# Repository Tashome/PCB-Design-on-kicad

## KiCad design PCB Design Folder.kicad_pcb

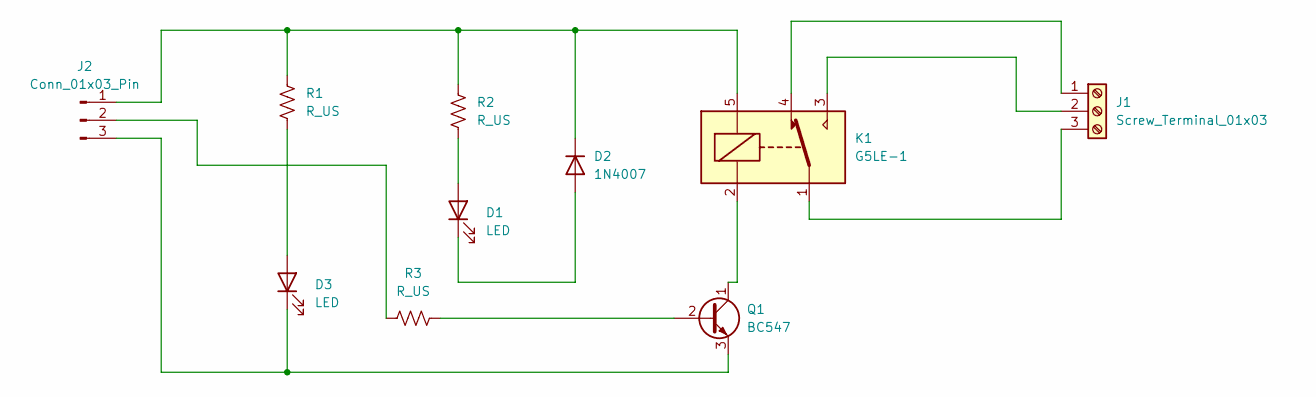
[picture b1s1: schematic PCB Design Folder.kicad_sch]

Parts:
D1, D3: LED; LED_D3.0mm
D2: 1N4007; D_DO-41_SOD81_P10.16mm_Horizontal
J1: Screw_Terminal_01x03; Altech_AK300_1x03_P5.00mm_45-Degree
J2: Conn_01x03_Pin; PinHeader_1x03_P1.27mm_Vertical_SMD_Pin1Left
K1: G5LE-1; Relay_SPDT_Omron-G5LE-1
Q1: BC547; TO-92_Inline
R1, R2, R3: R_US; R_Axial_DIN0204_L3.6mm_D1.6mm_P5.08mm_Horizontal

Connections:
unnamed: D1.2 (A), R2.2
unnamed: D1.1 (K), D2.2 (A)
unnamed: D2.1 (K), J2.1, K1.5, R1.1, R2.1
unnamed: D3.2 (A), R1.2
unnamed: D3.1 (K), J2.3, Q1.3 (E)
unnamed: J1.1, K1.4
unnamed: J1.2, K1.3
unnamed: J1.3, K1.1
unnamed: J2.2, R3.1
unnamed: Q1.2 (B), R3.2
unnamed: K1.2, Q1.1 (C)

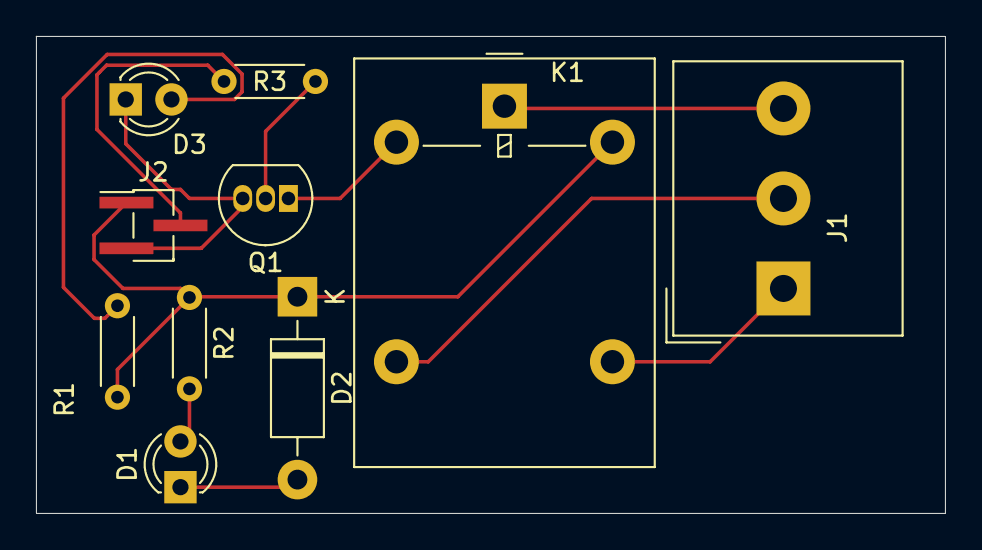
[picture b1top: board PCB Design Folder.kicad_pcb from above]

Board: 2 copper layers, 50.5 x 26.5 mm, 10 parts (0 on the bottom side), 11 nets.

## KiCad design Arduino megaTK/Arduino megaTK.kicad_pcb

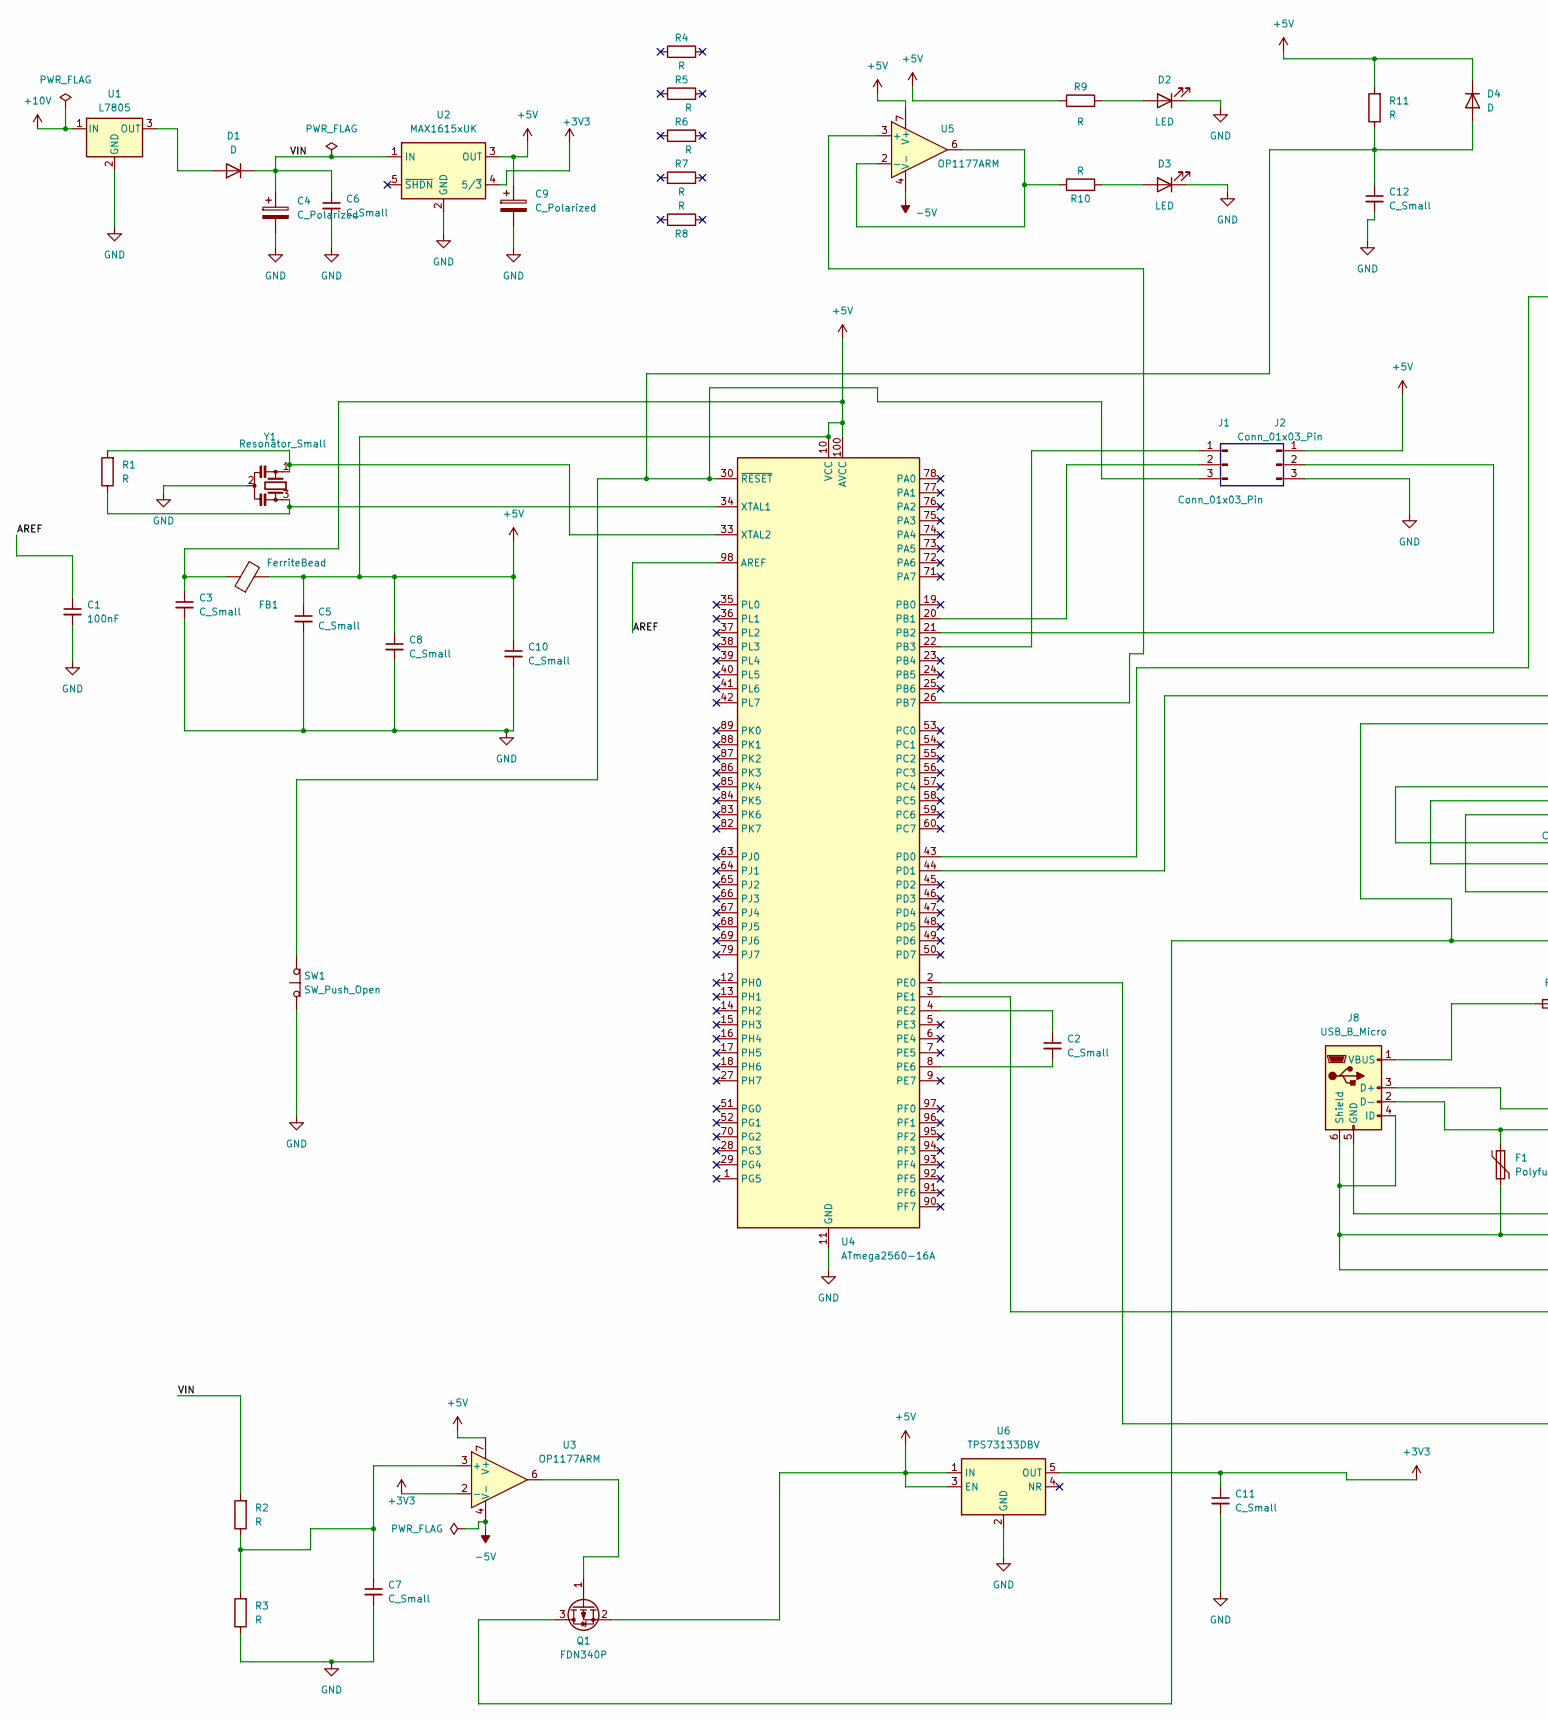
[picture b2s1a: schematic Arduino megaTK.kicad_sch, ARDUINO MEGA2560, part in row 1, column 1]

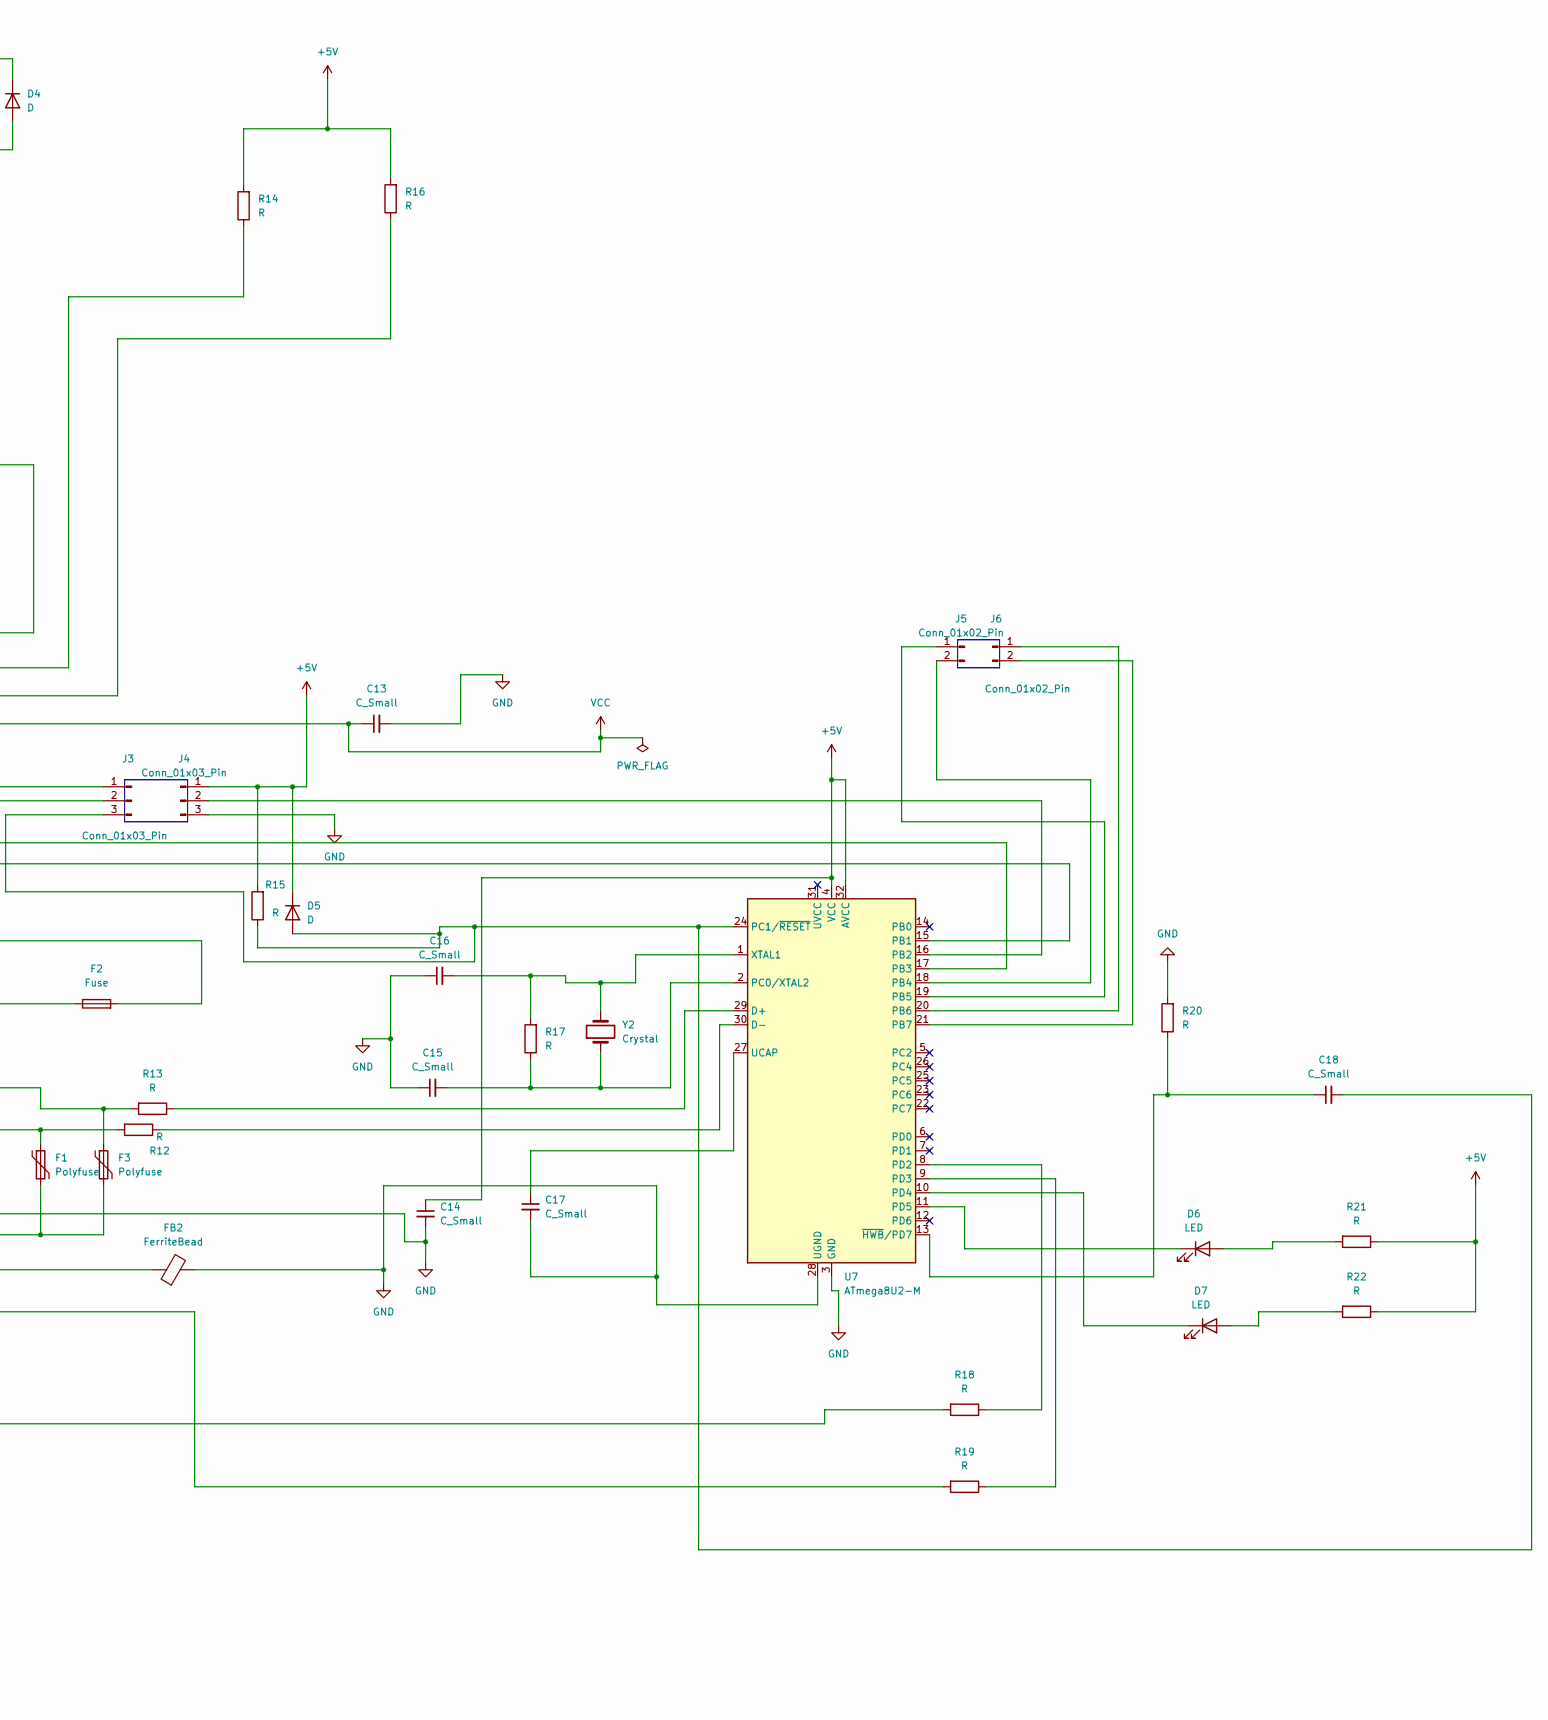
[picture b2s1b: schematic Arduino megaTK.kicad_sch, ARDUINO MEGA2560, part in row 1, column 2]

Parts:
C1: 100nF; C_0603_1608Metric
C2, C3, C5, C6, C7, C8, C10, C11, C12, C13, C14, C15, C16, C17, C18: C_Small; C_0603_1608Metric
C4, C9: C_Polarized; CP_Radial_D4.0mm_P1.50mm
D1, D4, D5: D; D_0805_2012Metric
D2, D3, D6, D7: LED; LED_0805_2012Metric_Pad1.15x1.40mm_HandSolder
F1, F3: Polyfuse; Fuse_1206_3216Metric_Pad1.42x1.75mm_HandSolder
F2: Fuse; Fuse_0603_1608Metric
FB1, FB2: FerriteBead; L_0603_1608Metric
J1, J2, J3, J4: Conn_01x03_Pin; PinHeader_1x03_P2.54mm_Vertical
J5, J6: Conn_01x02_Pin; PinHeader_1x02_P2.54mm_Vertical
J8: USB_B_Micro; USB_Mini-B_Lumberg_2486_01_Horizontal
Q1: FDN340P; SOT-23
R1, R2, R3, R4, R5, R6, R7, R8, R9, R10, R11, R12, R13, R14, R15, R16, R17, R18, R19, R20, R21, R22: R; R_0603_1608Metric
SW1: SW_Push_Open; SW_SPST_PTS645
U1: L7805; BarrelJack_Horizontal
U2: MAX1615xUK; SOT-23-5
U3, U5: OP1177ARM; MSOP-8_3x3mm_P0.65mm
U4: ATmega2560-16A; TQFP-100_14x14mm_P0.5mm
U6: TPS73133DBV; SOT-23-5
U7: ATmega8U2-M; QFN-32-1EP_5x5mm_P0.5mm_EP3.3x3.3mm_ThermalVias
Y1: Resonator_Small; Resonator_SMD-3Pin_7.2x3.0mm
Y2: Crystal; Resonator_SMD_Murata_CDSCB-2Pin_4.5x2.0mm

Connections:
+3V3: C11.1, U2.4 (5/~3), U3.2 (-), U6.5 (OUT)
+5V: C3.1, C5.1, C8.1, C9.1, C10.1, C14.1, D4.1 (K), D5.1 (K), FB1.1, FB1.2, J2.1, J4.1, Q1.2 (S), R9.1, R11.2, R14.2, R15.2, R16.2, R21.1, R22.1, U2.3 (OUT), U3.7 (V+), U4.10 (VCC), U4.31 (VCC), U4.61 (VCC), U4.80 (VCC), U4.100 (AVCC), U5.7 (V+), U6.1 (IN), U6.3 (EN), U7.4 (VCC), U7.32 (AVCC)
+10V: U1.1 (IN)
-5V: U3.4 (V-), U5.4 (V-)
/AREF: C1.1, U4.98 (AREF)
/VIN: C4.1, C6.1, D1.1 (K), R2.2, U2.1 (IN)
GND: C1.2, C3.2, C4.2, C5.2, C6.2, C7.2, C8.2, C9.2, C10.2, C11.2, C12.2, C13.2, C14.2, C15.1, C16.1, C17.2, D2.1 (K), D3.1 (K), FB2.2, J2.3, J4.3, J8.5 (GND), R3.1, R20.2, SW1.1 (A), U1.2 (GND), U2.2 (GND), U4.11 (GND), U4.32 (GND), U4.62 (GND), U4.81 (GND), U4.99 (GND), U6.2 (GND), U7.3 (GND), U7.28 (UGND), U7.33 (GND), Y1.2
unnamed: D1.2 (A), U1.3 (OUT)
unnamed: D2.2 (A), R9.2
unnamed: D3.2 (A), R10.2
unnamed: C12.1, D4.2 (A), J1.3, R11.1, SW1.2 (B), U4.30 (~RESET)
unnamed: C18.2, D5.2 (A), J3.3, R15.1, U7.24 (PC1/~RESET)
unnamed: D6.2 (A), R21.2
unnamed: D6.1 (K), U7.11 (PD5)
unnamed: D7.2 (A), R22.2
unnamed: D7.1 (K), U7.10 (PD4)
unnamed: J1.1, U4.22 (PB3)
unnamed: J1.2, U4.20 (PB1)
unnamed: J2.2, U4.21 (PB2)
unnamed: J3.1, U7.17 (PB3)
unnamed: J3.2, U7.15 (PB1)
unnamed: J4.2, U7.16 (PB2)
unnamed: J5.1, U7.19 (PB5)
unnamed: J5.2, U7.18 (PB4)
unnamed: J6.1, U7.20 (PB6)
unnamed: J6.2, U7.21 (PB7)
unnamed: F3.1, J8.3 (D+), R13.2
unnamed: F1.1, J8.2 (D-), R12.2
unnamed: F1.2, F3.2, FB2.1, J8.4 (ID), J8.6 (Shield)
unnamed: F2.1, J8.1 (VBUS)
unnamed: Q1.1 (G), U3.6
unnamed: C7.1, R2.1, R3.2, U3.3 (+)
unnamed: U4.26 (PB7), U5.3 (+)
unnamed: R14.1, U4.43 (PD0)
unnamed: R16.1, U4.44 (PD1)
unnamed: R18.2, U4.2 (PE0)
unnamed: R19.2, U4.3 (PE1)
unnamed: C2.1, U4.4 (PE2)
unnamed: C2.2, U4.8 (PE6)
unnamed: R1.1, U4.34 (XTAL1), Y1.3
unnamed: R1.2, U4.33 (XTAL2), Y1.1
unnamed: R10.1, U5.2 (-), U5.6
unnamed: R13.1, U7.29 (D+)
unnamed: R12.1, U7.30 (D-)
unnamed: C15.2, R17.1, U7.2 (PC0/XTAL2), Y2.1
unnamed: R18.1, U7.8 (PD2)
unnamed: R19.1, U7.9 (PD3)
unnamed: C17.1, U7.27 (UCAP)
unnamed: C16.2, R17.2, U7.1 (XTAL1), Y2.2
unnamed: C18.1, R20.1, U7.13 (~HWB/PD7)
VCC: C13.1, F2.2, Q1.3 (D)

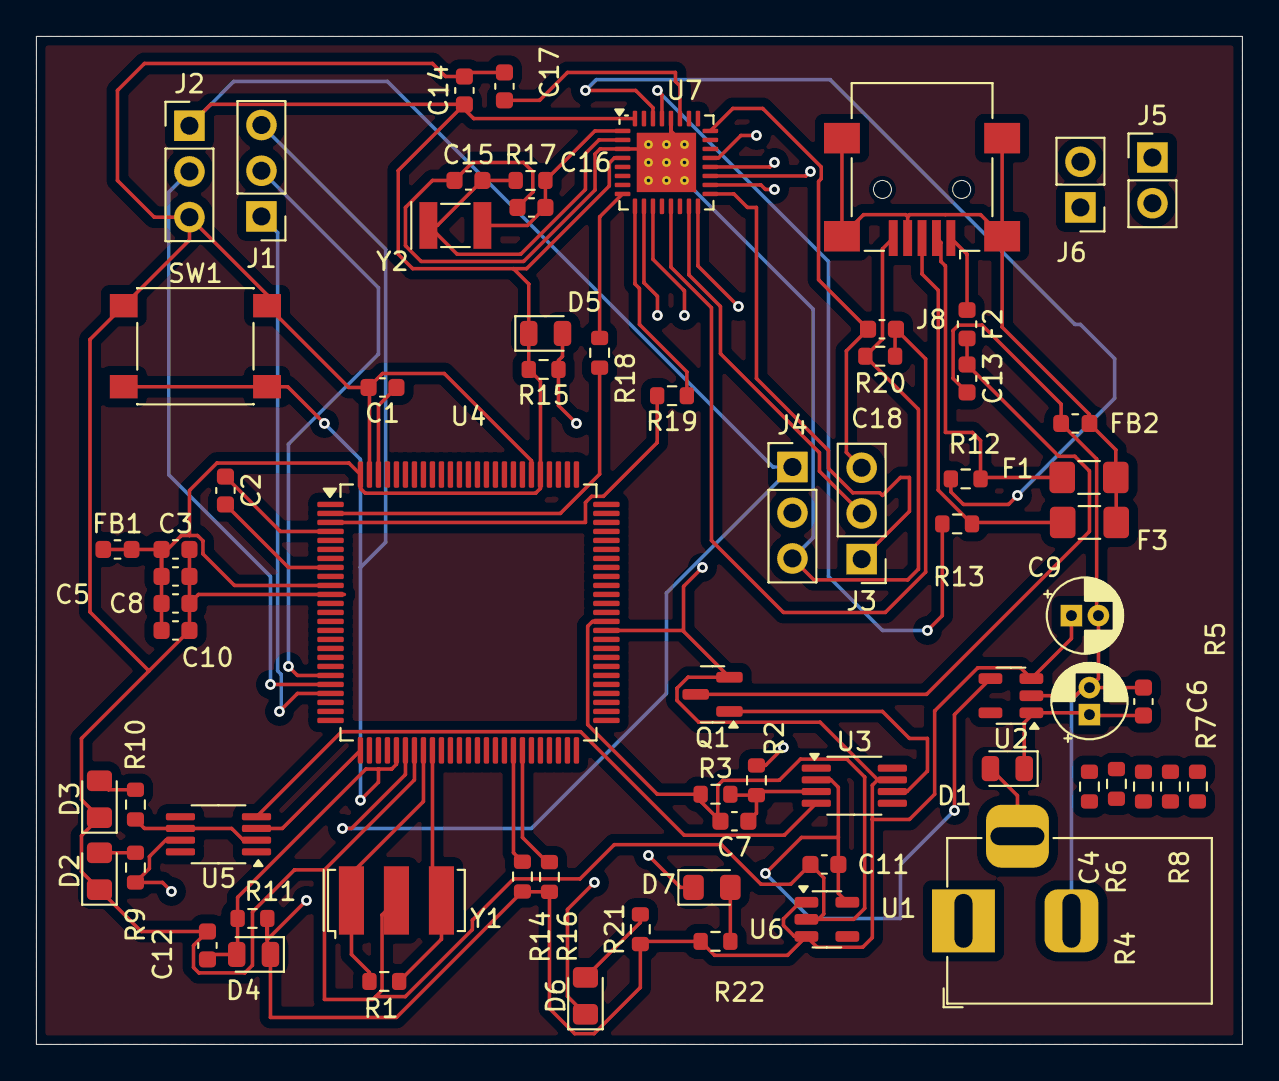
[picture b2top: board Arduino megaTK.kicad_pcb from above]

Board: 4 copper layers, 67.0 x 56.0 mm, 70 parts (0 on the bottom side), 50 nets.

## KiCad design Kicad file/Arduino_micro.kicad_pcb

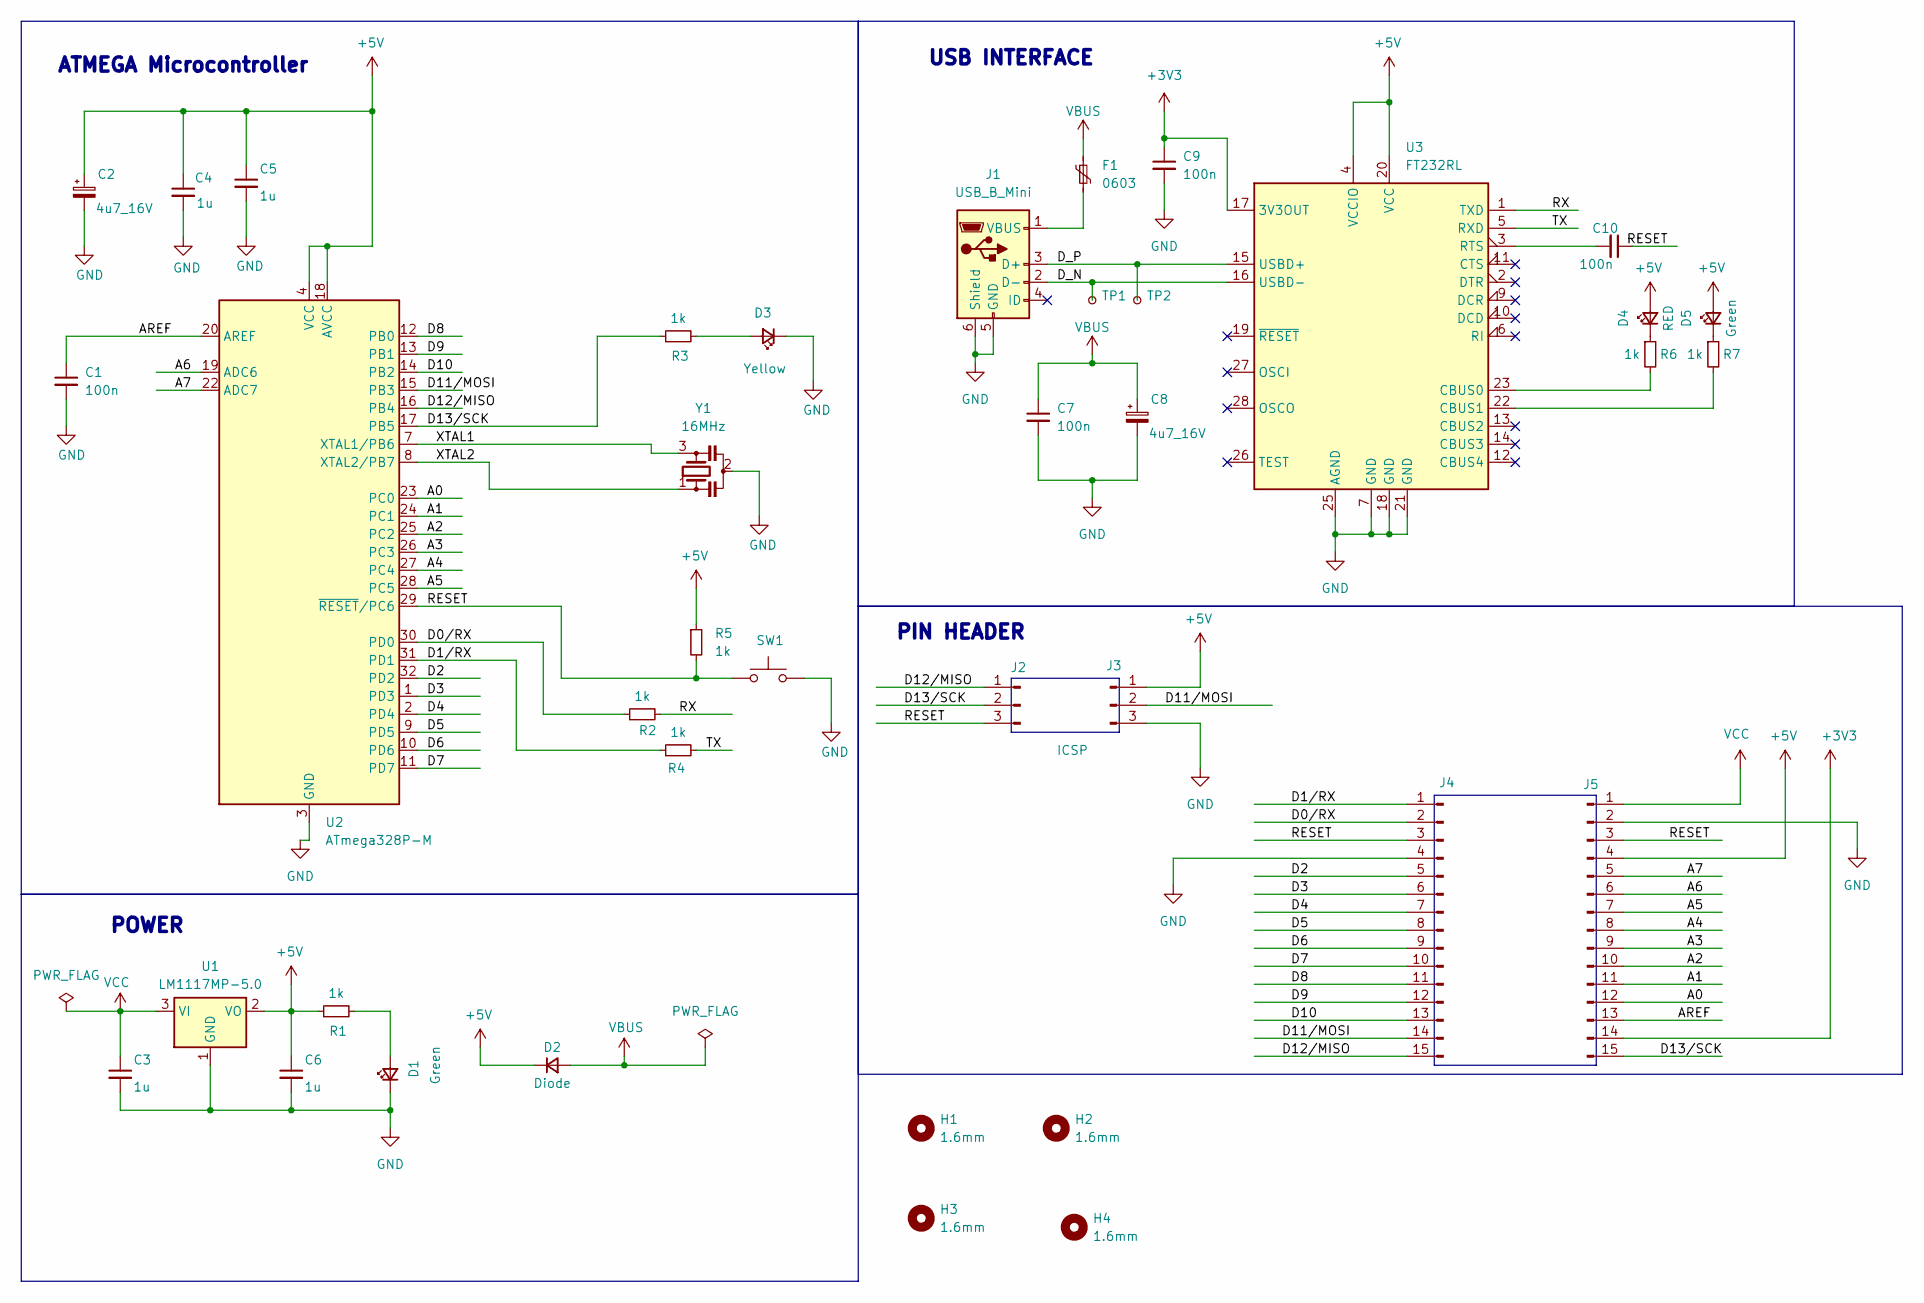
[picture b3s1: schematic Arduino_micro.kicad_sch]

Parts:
C1, C7, C9, C10: 100n; C_0603_1608Metric
C2, C8: 4u7_16V; CP_EIA-3216-10_Kemet-I
C3, C4, C5, C6: 1u; C_0603_1608Metric
D1, D5: Green; LED_0805_2012Metric
D2: Diode; D_MicroSMP_AK
D3: Yellow; LED_0805_2012Metric
D4: RED; LED_0805_2012Metric
F1: 0603; D_0603_1608Metric
H1, H2, H3, H4: 1.6mm; MountingHole_2mm
J1: USB_B_Mini; USB_Mini-B_Lumberg_2486_01_Horizontal
J2: PinHeader_1x03_P2.54mm_Vertical
J3: ICSP; PinHeader_1x03_P2.54mm_Vertical
J4, J5: PinHeader_1x15_P2.54mm_Vertical
R1, R2, R3, R4, R5, R6, R7: 1k; R_0603_1608Metric
SW1: SW_Push; SW_DIP_SPSTx01_Slide_9.78x4.72mm_W7.62mm_P2.54mm
TP1, TP2: TestPoint_Pad_D1.0mm
U1: LM1117MP-5.0; SOT-223-3_TabPin2
U2: ATmega328P-M; QFN-32-1EP_5x5mm_P0.5mm_EP3.1x3.1mm
U3: FT232RL; SSOP-28_5.3x10.2mm_P0.65mm
Y1: 16MHz; Resonator_SMD_Murata_CSTxExxV-3Pin_3.0x1.1mm

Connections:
+3V3: C9.1, J5.14, U3.17 (3V3OUT)
/A0: J5.12, U2.23 (PC0)
/A1: J5.11, U2.24 (PC1)
/A2: J5.10, U2.25 (PC2)
/A3: J5.9, U2.26 (PC3)
/A4: J5.8, U2.27 (PC4)
/A5: J5.7, U2.28 (PC5)
/A6: J5.6, U2.19 (ADC6)
/A7: J5.5, U2.22 (ADC7)
/AREF: C1.1, J5.13, U2.20 (AREF)
/D0/RX: J4.2, R2.1, U2.30 (PD0)
/D1/RX: J4.1, R4.1, U2.31 (PD1)
/D2: J4.5, U2.32 (PD2)
/D3: J4.6, U2.1 (PD3)
/D4: J4.7, U2.2 (PD4)
/D5: J4.8, U2.9 (PD5)
/D6: J4.9, U2.10 (PD6)
/D7: J4.10, U2.11 (PD7)
/D8: J4.11, U2.12 (PB0)
/D9: J4.12, U2.13 (PB1)
/D10: J4.13, U2.14 (PB2)
/D11/MOSI: J3.2, J4.14, U2.15 (PB3)
/D12/MISO: J2.1, J4.15, U2.16 (PB4)
/D13/SCK: J2.2, J5.15, R3.1, U2.17 (PB5)
/D_N: J1.2 (D-), TP1.1, U3.16 (USBD-)
/D_P: J1.3 (D+), TP2.1, U3.15 (USBD+)
/RESET: C10.1, J2.3, J4.3, J5.3, R5.2, SW1.1, U2.29 (~RESET/PC6)
/RX: R2.2, U3.1 (TXD)
/TX: R4.2, U3.5 (RXD)
/XTAL1: U2.7 (XTAL1/PB6), Y1.3
/XTAL2: U2.8 (XTAL2/PB7), Y1.1
GND: C1.2, C2.2, C3.2, C4.2, C5.2, C6.2, C7.2, C8.2, C9.2, D1.1 (K), D3.1 (K), J1.5 (GND), J1.6 (Shield), J3.3, J4.4, J5.2, SW1.2, U1.1 (GND), U2.3 (GND), U2.5 (GND), U2.21 (GND), U2.33 (GND), U3.7 (GND), U3.18 (GND), U3.21 (GND), U3.25 (AGND), Y1.2; also elsewhere on the board
unnamed: D1.2 (A), R1.2
unnamed: D3.2 (A), R3.2
unnamed: D4.1 (K), R6.1
unnamed: D5.1 (K), R7.1
unnamed: F1.2, J1.1 (VBUS)
unnamed: R6.2, U3.23 (CBUS0)
unnamed: R7.2, U3.22 (CBUS1)
unnamed: C10.2, U3.3 (RTS)
VCC: C3.1, J5.1, U1.3 (VI)

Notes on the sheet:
ATMEGA Microcontroller
PIN HEADER
USB INTERFACE
POWER

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
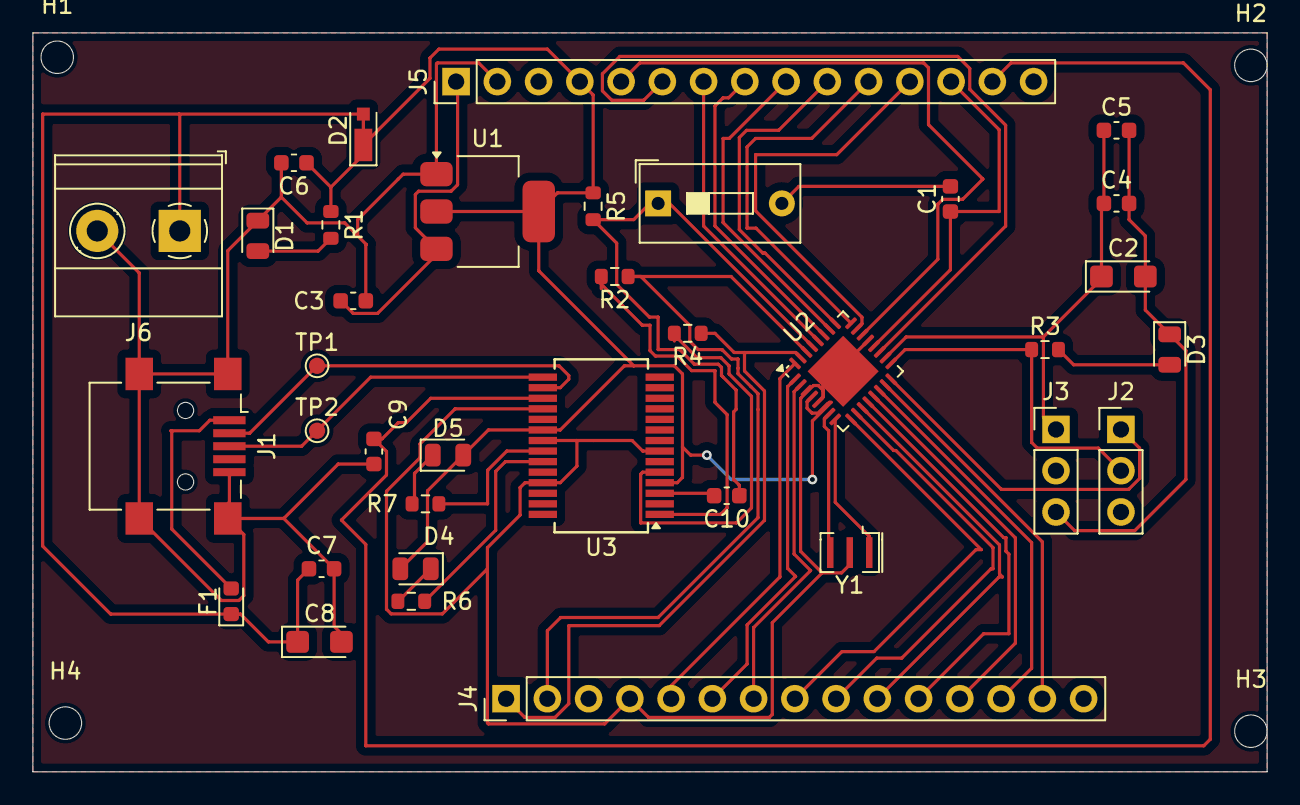
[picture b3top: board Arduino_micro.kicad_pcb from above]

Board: 4 copper layers, 76.0 x 45.5 mm, 40 parts (0 on the bottom side), 42 nets.

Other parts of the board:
J6: Screw_Terminal_01x02; TerminalBlock_Phoenix_MKDS-1,5-2-5.08_1x02_P5.08mm_Horizont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

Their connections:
GND: J6.2; also elsewhere on the board

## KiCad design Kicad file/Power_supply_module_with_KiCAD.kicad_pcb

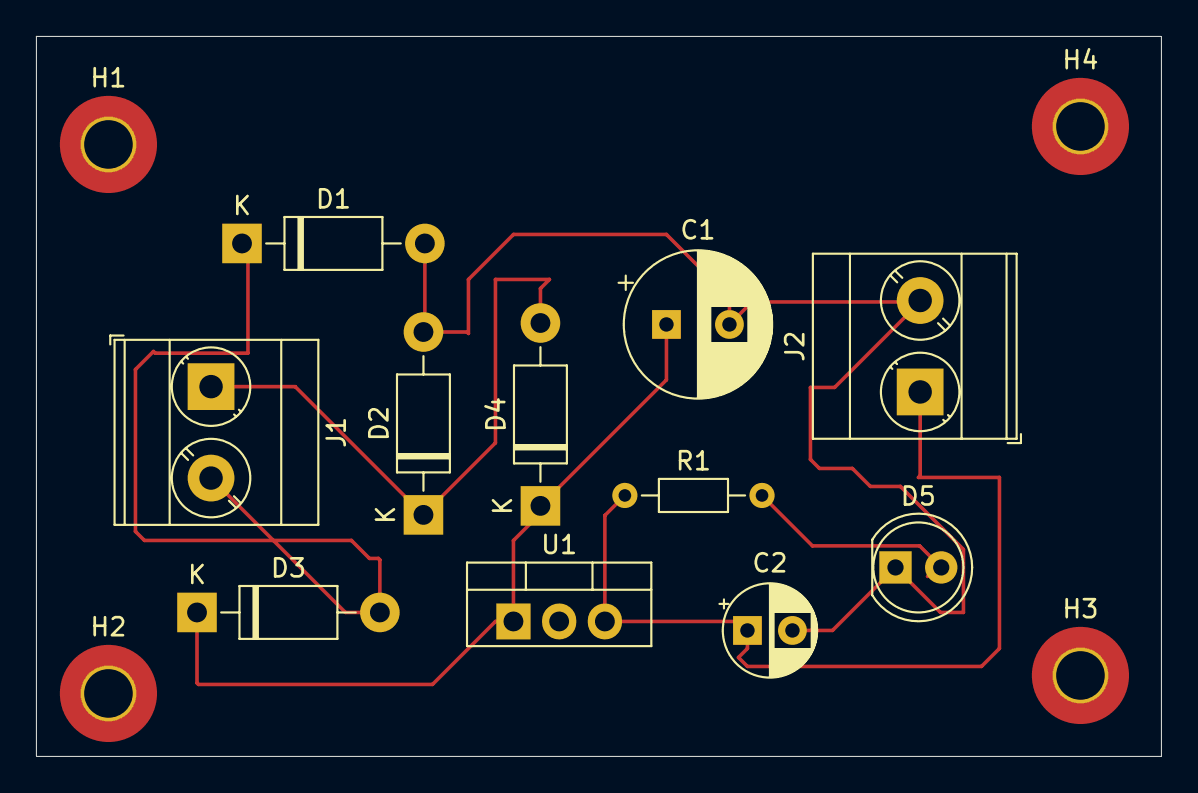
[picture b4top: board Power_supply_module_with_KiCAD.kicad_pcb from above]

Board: 2 copper layers, 62.5 x 40.0 mm, 15 parts (0 on the bottom side), 6 nets.

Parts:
C1: 470 uf 25v; CP_Radial_D8.0mm_P3.50mm
C2: 100 uf; CP_Radial_D5.0mm_P2.50mm
D1, D2, D3, D4: 1N4007; D_DO-41_SOD81_P10.16mm_Horizontal
D5: LED; LED_D5.0mm
H1, H2, H3, H4: MountingHole; MountingHole_2.7mm_M2.5_Pad_TopOnly
J1, J2: Screw_Terminal_01x02; TerminalBlock_Phoenix_MKDS-3-2-5.08_1x02_P5.08mm_Horizontal
R1: 1k; R_Axial_DIN0204_L3.6mm_D1.6mm_P7.62mm_Horizontal
U1: LM7805_TO220; TO-220-3_Vertical

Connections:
unnamed: C1.2, C2.2, D1.2 (A), D2.2 (A), D5.1 (K), J2.2
unnamed: D1.1 (K), D3.2 (A), J1.2
unnamed: D2.1 (K), D4.2 (A), J1.1
unnamed: C1.1, D3.1 (K), D4.1 (K), U1.1 (VI)
unnamed: D5.2 (A), R1.2
unnamed: C2.1, J2.1, R1.1, U1.3 (VO)

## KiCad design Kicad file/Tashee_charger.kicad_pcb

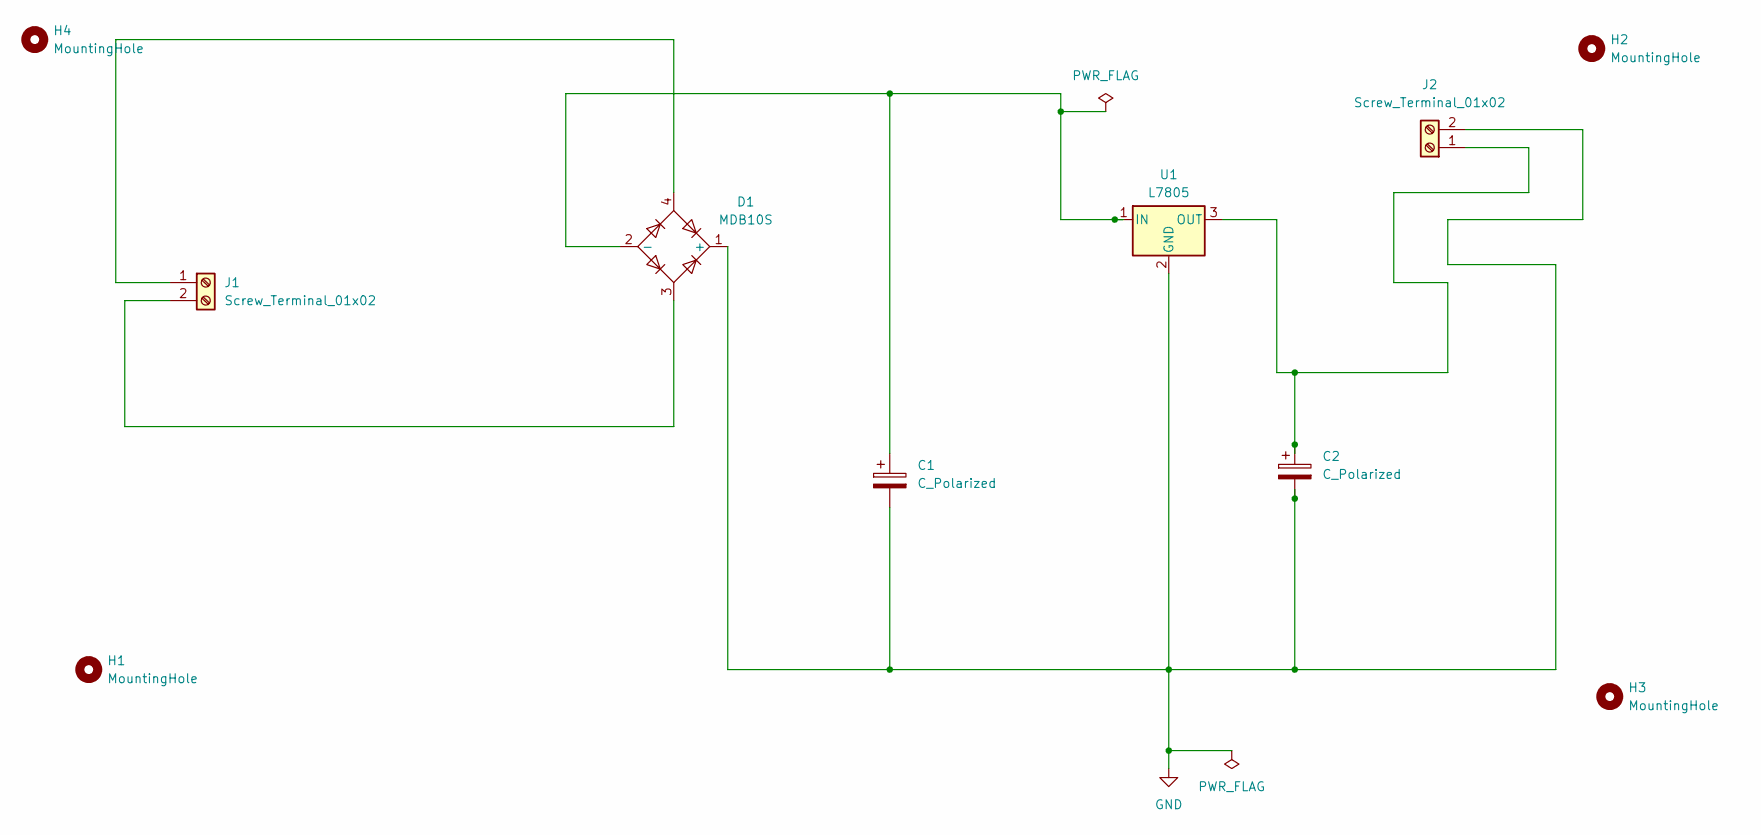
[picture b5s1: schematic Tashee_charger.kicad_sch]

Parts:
C1, C2: C_Polarized; CP_Radial_D6.3mm_P2.50mm
D1: MDB10S; TSSOP-4_4.4x5mm_P4mm
H1, H2, H3, H4: MountingHole; MountingHole_2mm
J1: Screw_Terminal_01x02; TerminalBlock_Phoenix_MKDS-1,5-2_1x02_P5.00mm_Horizontal
J2: Screw_Terminal_01x02; TerminalBlock_Phoenix_MKDS-3-2-5.08_1x02_P5.08mm_Horizontal
U1: L7805; TO-220F-3_Vertical

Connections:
unnamed: C1.2, C2.2, D1.1 (+), J2.2, U1.2 (GND)
unnamed: C1.1, D1.2 (-), U1.1 (IN)
unnamed: D1.4, J1.1
unnamed: D1.3, J1.2
unnamed: C2.1, J2.1, U1.3 (OUT)

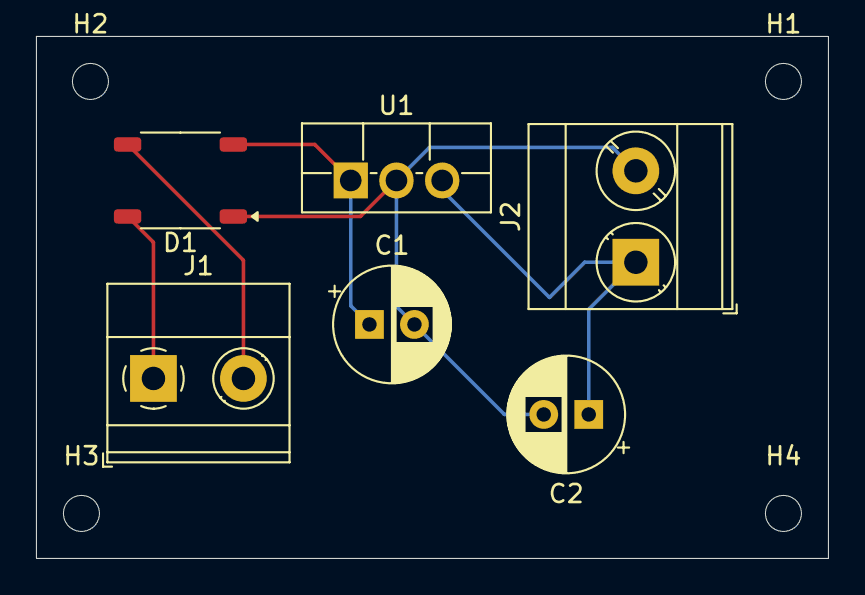
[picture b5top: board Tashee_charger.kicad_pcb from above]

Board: 2 copper layers, 44.0 x 29.0 mm, 10 parts (0 on the bottom side), 5 nets.
